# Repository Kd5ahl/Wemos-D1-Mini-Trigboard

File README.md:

# Wemos-D1-Mini-Trigboard

Kicad PCB Layout of an attempt to replicate the good work that Kevin Darrah (https://https://github.com/krdarrah) has done, but in the form factor of a Wemos D1 Mini

None of this has been tested, just an exercice in learning KiCad, and seeing if I could do it well enough.

As soon as Covid 19 dies down a bit, i will be ordering boards and parts.

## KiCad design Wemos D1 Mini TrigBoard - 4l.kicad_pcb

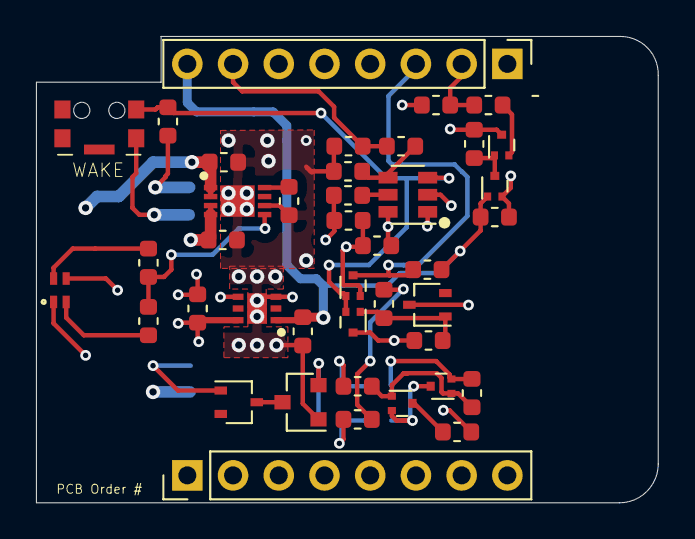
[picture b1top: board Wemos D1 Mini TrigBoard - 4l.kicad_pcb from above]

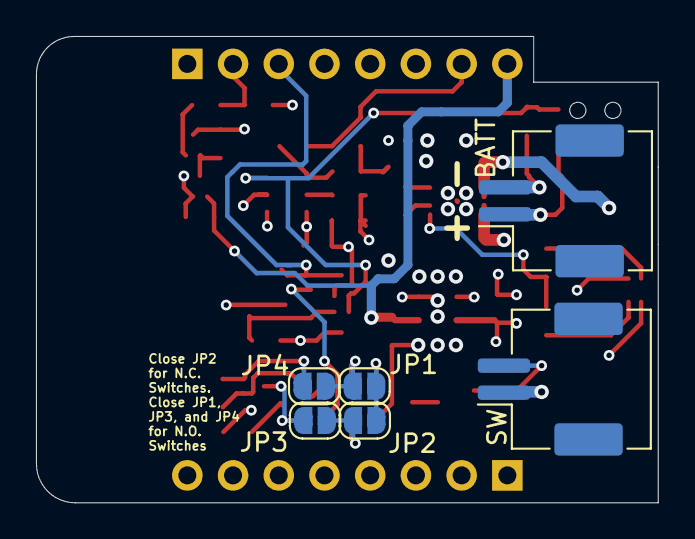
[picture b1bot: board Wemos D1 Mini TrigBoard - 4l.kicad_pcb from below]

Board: 4 copper layers, 34.5 x 25.9 mm, 47 parts (6 on the bottom side), 27 nets.

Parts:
C1, C9: 0.1u; C_0603_1608Metric
C2, C6: 1u; C_0603_1608Metric
C4, C5, C8: 10u; C_0603_1608Metric
C10, C11: C_Small; C_0603_1608Metric
D1, D2: BAT54W; SOT-323_SC-70
IC1: TPS73733DRVR; SON65P200X200X80-7N
IC2: MCP73831-5ACI_MC; SON50P300X200X100-9N-D
J1, J2: Conn_01x02_Male; JST_ZE_SM02B-ZESS-TB_1x02-1MP_P1.50mm_Horizontal
J3, J4: Conn_01x08_Male; PinHeader_1x08_P2.54mm_Vertical
JP1, JP2, JP3, JP4: SolderJumper_2_Open; SolderJumper-2_P1.3mm_Open_RoundedPad1.0x1.5mm
LED1: HSMF-C165; HSMF-C163
Q1, Q2, Q5: Q_PMOS_GSD; SOT-723
Q3, Q4, Q6: Q_NMOS_GSD; SOT-723
R1, R2, R3, R8, R9: 10k; R_0603_1608Metric
R4, R6, R7: 100; R_0603_1608Metric
R5: 100k; R_0603_1608Metric
R10, R11, R12, R13, R14, R15, R16: R_Small; R_0603_1608Metric
SW1: SW_Push; KMS233GPLFG
U1: TPS3839DBZ; SOT-23
U2: TPL5111; SOT-23-6

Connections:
+3V3: C2.2, IC1.1, J3.8, Q6.1, R8.2, R12.1
+5V: C10.2, IC2.1, IC2.2, J4.1, LED1.1
+BATT: C1.1, C6.2, C11.2, D2.3, IC1.6, IC2.3, IC2.4, J1.1, J2.1, Q1.3, Q5.3, R4.2, R5.2, R10.1, SW1.2, U2.1, U2.6
BAT_DIV_4P5: J3.2, R11.2, R13.1
DELAY: Q1.2, Q4.1, R6.1, SW1.1, U2.3
DONE: J3.7, R1.2, R2.1
DRVN: R3.1, U2.5
ENABLE: C5.1, IC1.4, R3.2
EXT_WAKE: J3.3, Q4.3, R8.1
GND: C1.2, C2.1, C4.2, C5.2, C6.1, C9.2, C10.1, C11.1, IC1.3, IC1.7, IC2.6, IC2.9, J2.2, J4.2, JP4.2, LED1.4, Q3.2, Q4.2, Q6.2, R2.2, R6.2, R12.2, R13.2, R14.2, U1.1, U2.2
unnamed: C4.1, R1.1, U2.4
unnamed: C8.1, D2.1, Q1.1, R5.1
unnamed: C8.2, R7.1
unnamed: C9.1, Q2.1, Q3.1, R9.1
unnamed: D1.1, J1.2
unnamed: D1.3, U1.3
unnamed: JP1.1, JP2.1, U1.2
unnamed: JP1.2, JP4.1, R9.2
unnamed: JP2.2, JP3.2, R7.2
unnamed: JP3.1, Q2.2, Q3.3
unnamed: LED1.2, R16.1
unnamed: LED1.3, R15.2
unnamed: Q2.3, R4.1
unnamed: Q5.1, Q6.3, R10.2
unnamed: Q5.2, R11.1
PROG: IC2.8, R14.1
STAT: IC2.5, R15.1, R16.2
